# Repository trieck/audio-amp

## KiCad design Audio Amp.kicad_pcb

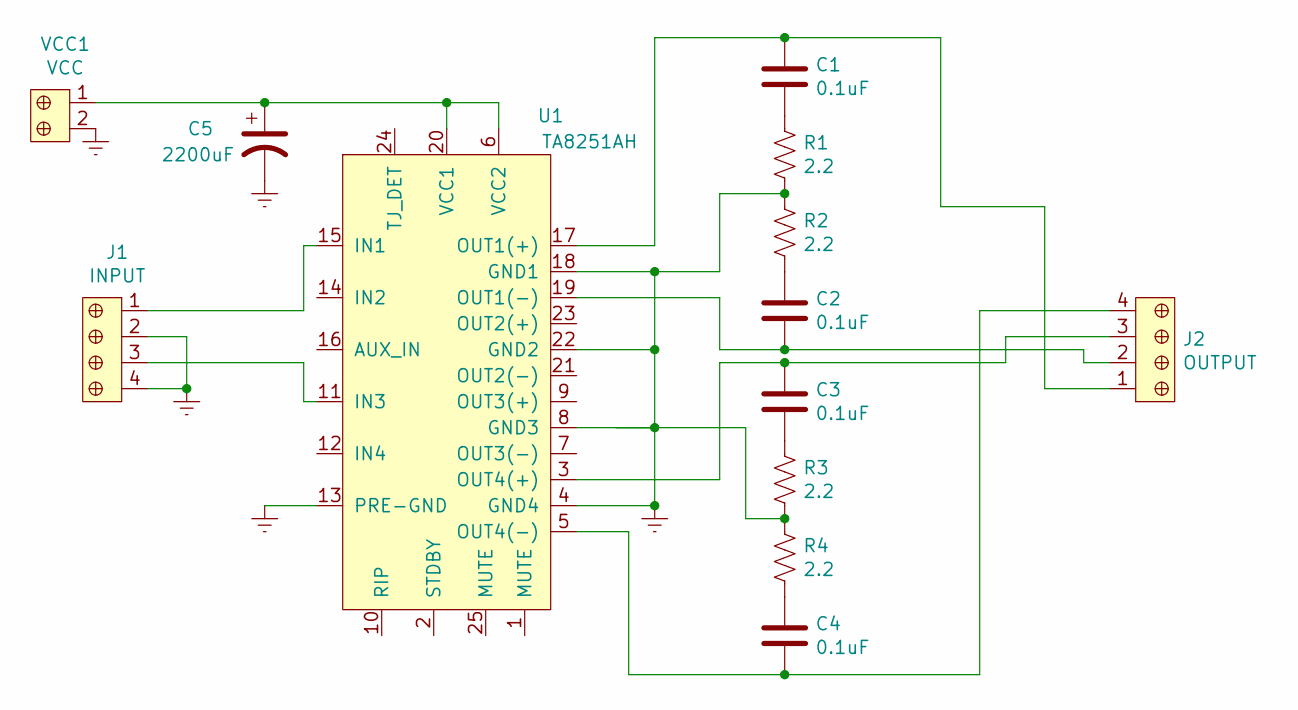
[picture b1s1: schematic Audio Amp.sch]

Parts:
C1, C2, C3, C4: 0.1uF; C_1206_3216Metric
C5: 2200uF; CP_Elec_18x17.5
J1: INPUT; PhoenixContact_MCV_1,5_4-G-3.5_1x04_P3.50mm_Vertical; MPN OSTTC040162; Digi-Key_PN ED2602-ND
J2: OUTPUT; PhoenixContact_MCV_1,5_4-G-3.5_1x04_P3.50mm_Vertical; MPN OSTTC040162; Digi-Key_PN ED2602-ND
R1, R2, R3, R4: 2.2; R_1206_3216Metric
U1: TA8251AH; HZIP25-P-1.27
VCC1: VCC; PhoenixContact_MCV_1,5_2-G-3.5_1x02_P3.50mm_Vertical; MPN 1935161; Digi-Key_PN 277-1667-ND

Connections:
Earth: C5.2, J1.2, J1.4, R1.2, R2.1, R3.2, R4.1, U1.4 (GND4), U1.8 (GND3), U1.13 (PRE-GND), U1.18 (GND1), U1.22 (GND2), VCC1.2
unnamed: C1.1, J2.1, U1.17 (OUT1(+))
unnamed: C1.2, R1.1
unnamed: C2.1, R2.2
unnamed: C2.2, J2.2, U1.19 (OUT1(-))
unnamed: C3.1, J2.3, U1.3 (OUT4(+))
unnamed: C3.2, R3.1
unnamed: C4.1, R4.2
unnamed: C4.2, J2.4, U1.5 (OUT4(-))
unnamed: C5.1, U1.6 (VCC2), U1.20 (VCC1), VCC1.1
unnamed: J1.1, U1.15 (IN1)
unnamed: J1.3, U1.11 (IN3)

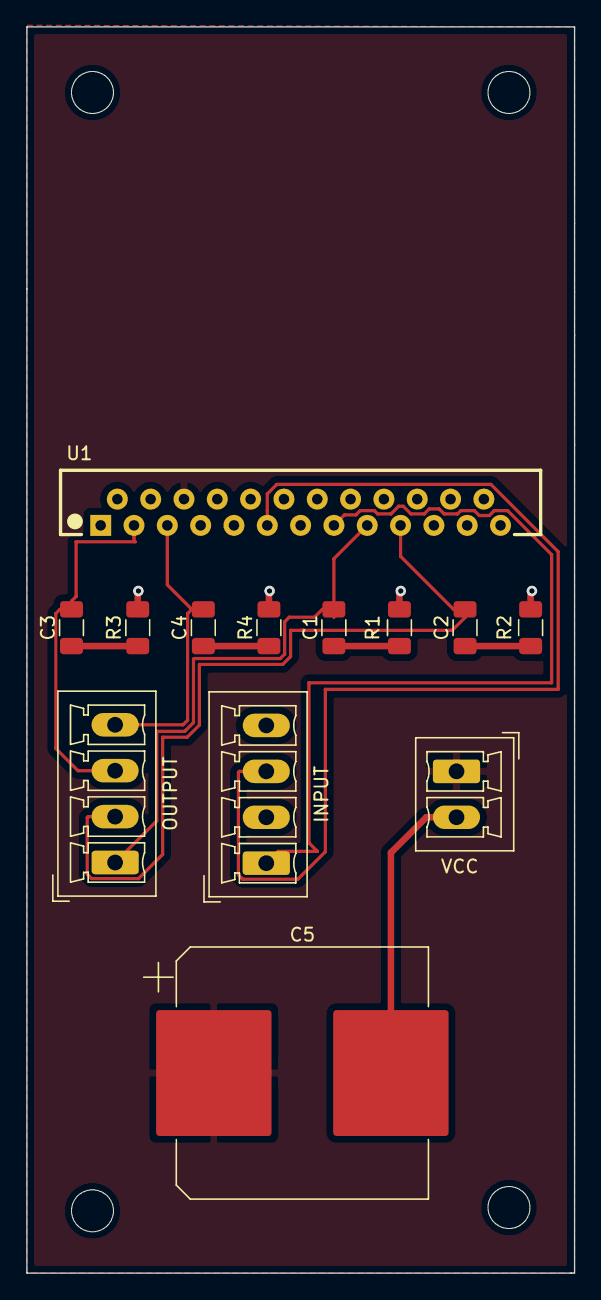
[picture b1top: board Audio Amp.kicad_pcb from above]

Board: 2 copper layers, 41.8 x 95.0 mm, 13 parts (0 on the bottom side), 12 nets.

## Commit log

2022-05-22 Initial commit.
2022-05-22 Update footprints
2022-06-01 Add cache files.
